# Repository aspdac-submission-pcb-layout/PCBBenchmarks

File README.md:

# A note for ASP-DAC 2021 reviewers

This repository was prepared from the original. The authors of contributed to many of these design. Therefore, some, but not all, license and author information was removed for review blinding. Some example license and author information that was not removed is located in the individual directories for each design (for example [bm1/bm1.license.txt](bm1/bm1.license.txt))

The unblinded repository contains full license and author citations for all designs.

# PCBBenchmarks

KiCad PCB benchmarks for automated layout.

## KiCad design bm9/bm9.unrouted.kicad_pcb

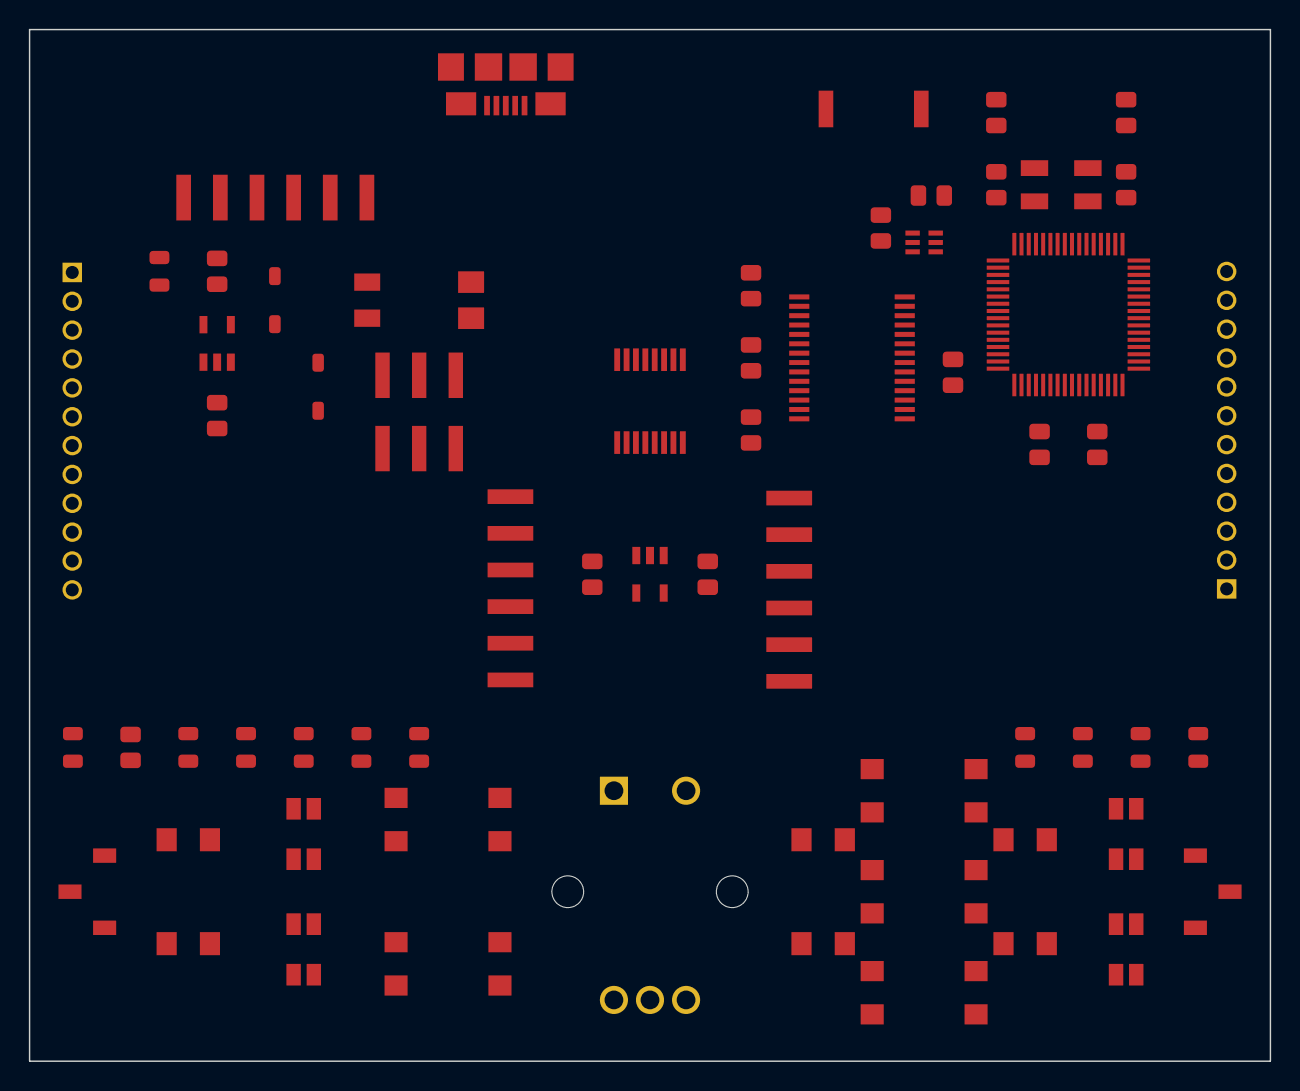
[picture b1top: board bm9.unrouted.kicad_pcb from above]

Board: 4 copper layers, 86.0 x 71.5 mm, 61 parts (0 on the bottom side), 63 nets, no tracks yet.

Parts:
A1: ANTENNA-CHIP; ANT-2.4GHZ-6.5X2.2MM
B1, B4, B5, B6, B7, B8, B9, B10: PUSHBUTTON_-4.5X4.5; 4.5MM_TACTILE_SWITCH_TL3305AF160QG
B2: BALUN0805; BALUN
B3: BATTERY-SPRING-SMD; WIRE-TERMINAL-1X2-2.5MM-SMD-AVX-009276002021106
C1, C8, C9: 0.1uF; CAPC2012X140_HS
C2: 0.75pF; CAPC2012X140_HS
C3: 22pF; CAPC2012X140_HS
C4, C10, C11, C12, C13, C16, C17: 1uF; CAPC2012X140_HS
C5, C6, C7: 10uF; CAPC2012X140_HS
C14, C15: 12pF; CAPC2012X140_HS
D1, D4, D5, D6: LED-2X-GREEN_RED; LED-2X-LTST-C155
D2, D3: 360mV; SOD3716X135_HS
E1: ROTARY-ENCODER-W_BUTTON-BOURNS-PEC12R-4217F; BOURNS-PEC12R
J1: USB-MICROA-AMPHENOL-10118192-0001LF; USB-MICROA-10118192-0001LF
J2, J3: 2.4K; JST-13-PTH
J4: AVR_SPI_PRG_6-SMD; 2X3-SMD
J7, J8: FRSKY-GIMBAL-2X-SERVO-SMD; 2X-SERVO-SMD
JP1: FTDI_BASIC-SMD; FTDI-BASIC-SMD
R1, R3, R13, R14, R15, R16, R17, R18: 510; RESC2012X60_HS
R2: 10K; RESC2012X60_HS
R7: 2.2K; RESC2012X60_HS
R8: 1.2K; RESC2012X60_HS
S1, S2: POWER-SWITCH-MFS201N-9-Z-SMD-VERTICAL; JS102011JCQN
U1: 3.3V; SOT23-DBV
U2: MCP73831T-2ACI/OT; SOT23-5
U3: FT232RLSSOP; SSOP28DB
U4: ATMEGA128RFA1; QFN-64
U5: DPDT-X2; SOP65P640X110-16
Y1: CRYSTAL5X3; CRYSTAL-SMD-5X3

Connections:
3V3: C12.1, C16.1, C17.1, D4.A2, J4.2, JP1.VCC, R2.2, R8.2, R13.2, R14.2, S2.1, U1.5, U4.23, U4.34, U4.44, U4.54, U4.59, U5.16
/BTN1/SCL: B4.3, B4.4, U4.25
/BTN2/SDA: B5.3, B5.4, U4.26
/BTN_CENTER: B9.1, B9.2, U4.53
/BTN_DOWN: B10.1, B10.2, U4.28
/BTN_LEFT: B7.1, B7.2, U4.51
/BTN_RIGHT: B8.1, B8.2, U4.52
/BTN_UP: B6.1, B6.2, U4.50
/CTS: U3.11, U5.2
/CTS-1: JP1.CTS, U5.1
/DTR: U3.2, U5.14
/DTR-0: C1.2, U5.15
/DTR-1: JP1.DTR, U5.13
/E1-A: E1.A, U4.40
/E1-B: E1.B, U4.41
/E1-BUT: E1.BUTA, U4.27
/FTDI_OUT: C4.2, C9.1, U3.4, U3.17
/GREF: J2.1, J2.4, J3.1, J3.4, J7.1, J7.4, J8.1, J8.4, R8.1
/MISO: J4.1, U4.39
/MOSI: J4.4, U4.38
/PITCH: J3.V, J8.V, U4.2
/RESET: B1.1, B1.2, C1.1, J4.5, R2.1, U4.12
/RF: D4.A1, U4.16
/ROLL: J3.H, J8.H, U4.1
/RXI: U3.5, U5.10
/RXI-0: U4.47, U5.11
/RXI-1: JP1.RXI, U5.9
/RXLED: D5.C2, U3.22
/SCK: J4.3, U4.37
/THROTTLE: J2.V, J7.V, U4.64
/TXLED: D5.C1, U3.23
/TXO: U3.1, U5.6
/TXO-0: U4.46, U5.7
/TXO-1: JP1.TXO, U5.5
/USB_D_N: J1.2, U3.16
/USB_D_P: J1.3, U3.15
/VBUS: C5.1, D1.A2, D2.A, J1.1, U2.4
/VREG_IN: C7.1, C8.1, C10.1, S1.1, U1.1, U1.3, U3.20
/YAW: J2.H, J7.H, U4.63
GND: B1.3, B1.4, B2.5, B3.2A, B3.2B, B4.1, B4.2, B5.1, B5.2, B6.3, B6.4, B7.3, B7.4, B8.3, B8.4, B9.3, B9.4, B10.3, B10.4, C2.2, C3.1, C4.1, C5.2, C6.2, C7.2, C8.2, C9.2, C10.2, C11.2, C12.2, C13.2, C14.2, C15.2, C16.2, C17.2, D1.C1, E1.BUTB, E1.C, J1.5, J1.6, J1.7, J1.8, J1.9, J1.10, J1.11, J2.3, J2.6, J3.3, J3.6, J4.6, J7.3, J7.6, J8.3, J8.6, JP1.GND, R7.2, R15.1, R16.1, R17.1, R18.1, S2.3, U1.2, U2.2, U3.7, U3.18, U3.21, U3.25, U3.26, U4.7, U4.10, U4.11, U4.20, U4.24, U4.33, U4.35, U4.45, U4.55, U4.58, U4.61, U5.8
unnamed: A1.FEED, B2.1, C2.1
unnamed: B2.2, C3.2
unnamed: B2.3, U4.9
unnamed: B2.4, U4.8
unnamed: B3.1A, B3.1B, C6.1, D3.A, U2.3
unnamed: C11.1, U4.21, U4.22
unnamed: C13.1, U4.60
unnamed: C14.1, U4.57, Y1.3
unnamed: C15.1, U4.56, Y1.1
unnamed: D1.A1, R3.1
unnamed: D1.C2, R1.1
unnamed: D4.C1, R15.2
unnamed: D4.C2, R16.2
unnamed: D5.A1, R14.1
unnamed: D5.A2, R13.1
unnamed: D6.A1, U4.15
unnamed: D6.A2, U4.14
unnamed: D6.C1, R18.2
unnamed: D6.C2, R17.2
unnamed: R1.2, R3.2, U2.1
unnamed: R7.1, U2.5
unnamed: S2.2, U5.4, U5.12
VBAT: D2.C, D3.C, S1.2

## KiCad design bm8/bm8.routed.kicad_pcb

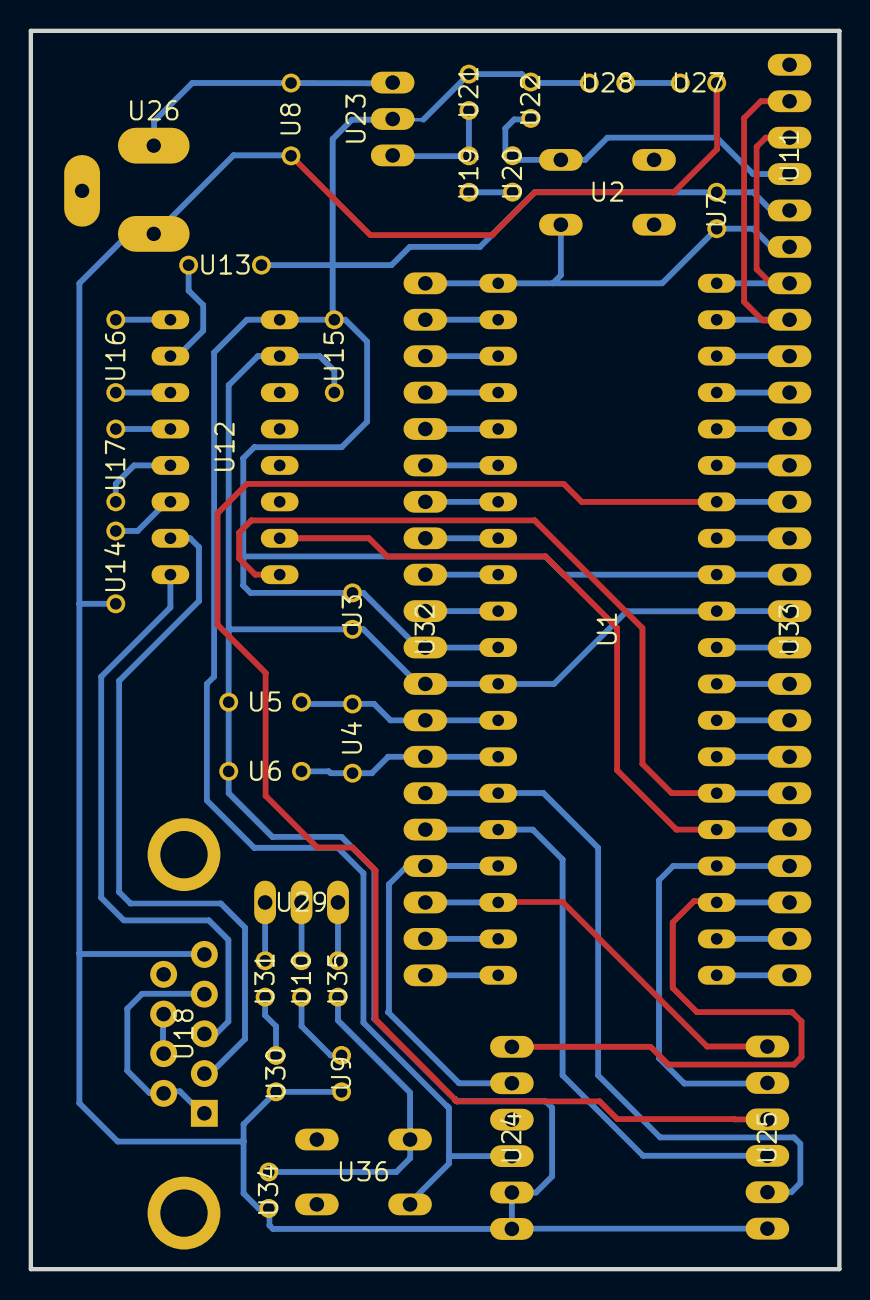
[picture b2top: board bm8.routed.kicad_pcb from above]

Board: 2 copper layers, 56.4 x 86.4 mm, 36 parts (0 on the bottom side), 58 nets.

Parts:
U1: DIL40
U2, U36: B3F-10XX
U3, U22: C025-024X044
U4: HC49_S
U5, U6, U13, U14, U15, U16, U17: C050-024X044
U7, U10, U19, U20, U21, U28, U31, U34, U35: V526-0
U8: C050-025X075
U9, U27, U30: LED3MM
U11, U24, U25: 1X06
U12: DIL16
U18: DB9
U23: 317TS
U26: 733980-62
U29: MA03-1
U32, U33: MA20-1

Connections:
/3.3V_SRC: U1.11, U1.32, U3.1, U7.1, U11.2, U12.16, U13.2, U15.1, U21.2, U22.1, U23.2, U24.3, U28.1, U32.10, U33.9, U36.1
/MRF_CS: U1.17, U24.5, U32.4
/MRF_INT: U1.34, U25.3, U33.7
/MRF_RESET: U1.15, U25.5, U32.6
/MRF_SCK: U1.18, U25.1, U32.3
/MRF_SDI: U1.23, U24.6, U33.18
/MRF_SDO: U1.24, U25.2, U33.17
/MRF_WAKE: U1.16, U25.4, U32.5
/N$17: U1.26, U12.9, U33.15
/N$21: U1.25, U12.10, U33.16
/OS1: U1.13, U4.1, U5.1, U32.8
/OSC2: U1.14, U4.2, U6.1, U32.7
GND: U1.12, U1.31, U2.1, U3.2, U5.2, U6.2, U8.2, U9.K, U11.3, U12.15, U14.1, U15.2, U18.5, U20.1, U22.2, U24.1, U24.2, U25.6, U26.1, U27.K, U30.K, U32.9, U33.10, U34.2
unnamed: U12.2, U13.1
unnamed: U12.6, U14.2
unnamed: U12.1, U16.1
unnamed: U12.3, U16.2
unnamed: U12.4, U17.1
unnamed: U12.5, U17.2
unnamed: U8.1, U23.3, U26.2
unnamed: U12.7, U18.2
unnamed: U12.8, U18.3
unnamed: U1.1, U2.3, U7.2, U11.1, U32.20
unnamed: U1.2, U32.19
unnamed: U1.3, U32.18
unnamed: U1.4, U32.17
unnamed: U1.5, U32.16
unnamed: U1.6, U32.15
unnamed: U1.7, U32.14
unnamed: U1.8, U32.13
unnamed: U1.9, U32.12
unnamed: U1.10, U32.11
unnamed: U1.19, U32.2
unnamed: U1.20, U32.1
unnamed: U1.21, U33.20
unnamed: U1.22, U33.19
unnamed: U1.27, U33.14
unnamed: U1.28, U33.13
unnamed: U1.29, U33.12
unnamed: U1.30, U33.11
unnamed: U1.33, U33.8
unnamed: U1.35, U33.6
unnamed: U1.36, U33.5
unnamed: U1.37, U33.4
unnamed: U1.38, U33.3
unnamed: U1.39, U11.5, U33.2
unnamed: U1.40, U11.4, U33.1
unnamed: U19.2, U21.1, U23.1
unnamed: U27.A, U28.2
unnamed: U30.A, U31.2
unnamed: U9.A, U10.2
unnamed: U34.1, U35.2, U36.3
unnamed: U29.3, U35.1
unnamed: U10.1, U29.2
unnamed: U29.1, U31.1
unnamed: U19.1, U20.2
unnamed: U18.1, U18.4, U18.6
unnamed: U18.7, U18.8

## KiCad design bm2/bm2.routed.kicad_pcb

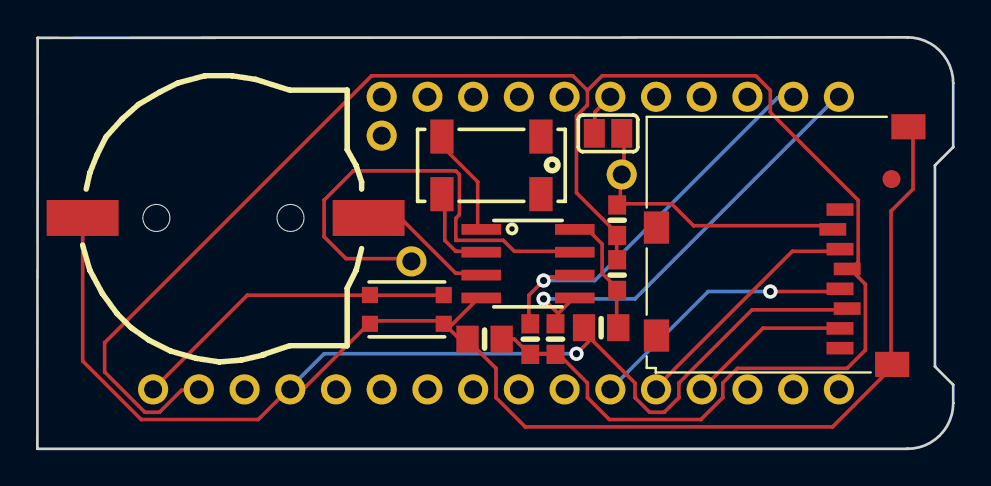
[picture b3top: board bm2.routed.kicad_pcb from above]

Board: 2 copper layers, 50.9 x 22.9 mm, 18 parts (0 on the bottom side), 15 nets.

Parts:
B1: cr1220; CR1220-2
C1, C2: 10uF; 0805-NO
FID1: FIDUCIAL_1MM
IC1: PCF8523T; SOIC8_150MIL
INT1: 1X01_ROUND
JP1: 1X11_ROUND
JP2: 1X16_ROUND
JP3: 1X01_ROUND
R1, R2: 10K; 0603-NO
R3: 100K; 0603-NO
R4: 1K; 0603-NO
SDCS: 1X01_ROUND
SJ1: SOLDERJUMPER_CLOSEDWIRE
SW1: KMR2; BTN_KMR2_4.6X2.8
X4: microsd; MICROSD
Y1: 32khz; CRYSTAL_8X3.8

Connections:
+3V3: C2.1, JP2.15, R1.2, R2.2, R3.2, R4.1, X4.4
CR1220: B1.+, IC1.3
CS: JP1.6, SJ1.1
GND: B1.-, C1.2, C2.2, IC1.4, JP2.13, SW1.A, SW1.A', X4.6, X4.MT1, X4.MT2
INT1: IC1.7, INT1.1
MISO: JP2.4, X4.7
MOSI: JP2.5, X4.3
unnamed: C1.1, IC1.8, R4.2
unnamed: IC1.1, Y1.P$4
unnamed: IC1.2, Y1.P$1
RESET: JP2.16, SW1.B, SW1.B'
SCK: JP2.6, X4.5
SCL: IC1.6, JP1.10, R2.1
SDA: IC1.5, JP1.11, R1.1
SD_CS: R3.1, SDCS.1, SJ1.2, X4.2

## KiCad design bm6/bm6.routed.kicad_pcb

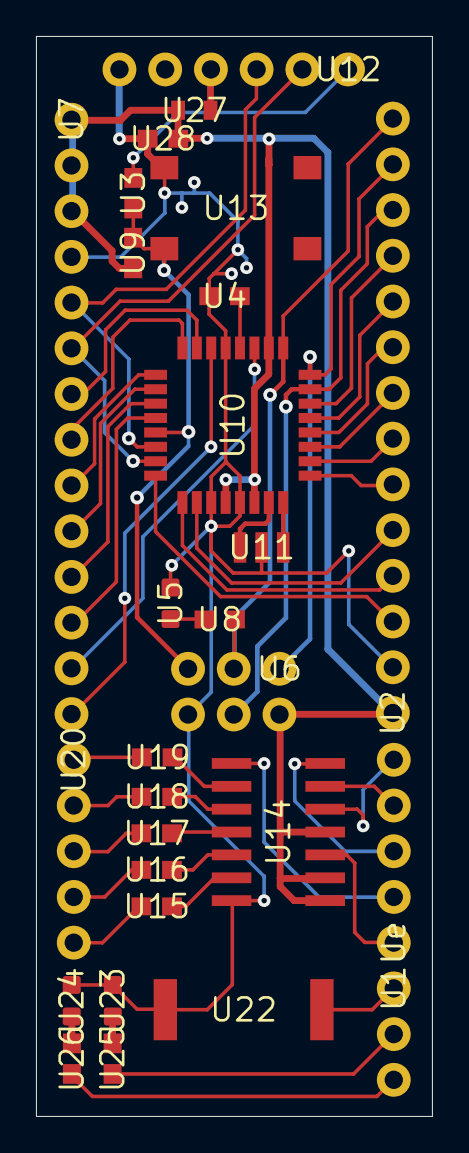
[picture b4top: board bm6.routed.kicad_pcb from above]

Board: 2 copper layers, 22.0 x 60.0 mm, 28 parts (0 on the bottom side), 51 nets.

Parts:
U1: 1X03
U2, U7: 1X14
U3, U4, U8, U9, U15, U16, U17, U18, U19, U25, U26, U28: 0603
U5, U23, U24: LED-0603
U6: 2X3
U10: TQFP32-08
U11: RESONATOR-SMD
U12: FTDI_BASIC
U13: TACTILE_SWITCH_SMD_6.2MM_TALL
U14: SO14
U20: 1X05
U22: PKMCS
U27: FUSC1608X100N
Ue: 1X05

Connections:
/A0: U7.7, U10.23
/A1: U7.8, U10.24
/A2: U7.9, U10.25
/A3: U7.10, U10.26
/A4: U7.11, U10.27
/A5: U7.12, U10.28
/A6: U7.13, U10.19
/A7: U7.14, U10.22
/D2: U2.3, U10.32
/D3: U2.4, U10.1
/D4: U2.5, U10.2
/D5: U2.6, U10.9
/D6: U2.7, U10.10
/D7: U2.8, U10.11
/D8: U2.9, U10.12
/D9: U2.10, U10.13
/D10: U2.11, U10.14
/DTR: U3.1, U12.DTR
/GO: U14.3, Ue.1
/MISO: U2.13, U6.1, U10.16
/MOSI: U2.12, U6.4, U10.15
/OUT1: U14.8, Ue.2
/OUT2: U14.7, Ue.3
/OUT3: U14.6, Ue.4
/OUT4: U14.5, Ue.5
/RST: U3.2, U6.5, U9.1, U10.29, U13.B2
/RXI: U7.5, U10.30, U12.TXO
/SCK: U2.14, U6.3, U8.1, U10.17
/TXO: U7.6, U10.31, U12.RXI
GND: U2.2, U4.2, U5.C, U6.6, U7.4, U10.3, U10.5, U10.21, U11.2, U12.GND, U13.A2, U14.14, U22.1, U23.C, U24.C, U28.2
unnamed: U4.1, U10.20
unnamed: U5.A, U8.2
unnamed: U23.A, U25.1
unnamed: U24.A, U26.1
unnamed: U12.VCC, U27.1
unnamed: U14.9, U19.2
unnamed: U14.10, U18.2
unnamed: U14.11, U17.2
unnamed: U14.12, U16.2
unnamed: U14.13, U15.2
unnamed: U19.1, U20.1
unnamed: U18.1, U20.2
unnamed: U17.1, U20.3
unnamed: U16.1, U20.4
unnamed: U15.1, U20.5
unnamed: U1.1, U22.2
unnamed: U1.2, U25.2
unnamed: U1.3, U26.2
unnamed: U10.7, U11.3
unnamed: U10.8, U11.1
VCC: U2.1, U6.2, U7.1, U7.2, U7.3, U9.2, U10.4, U10.6, U10.18, U14.1, U14.2, U14.4, U27.2, U28.1

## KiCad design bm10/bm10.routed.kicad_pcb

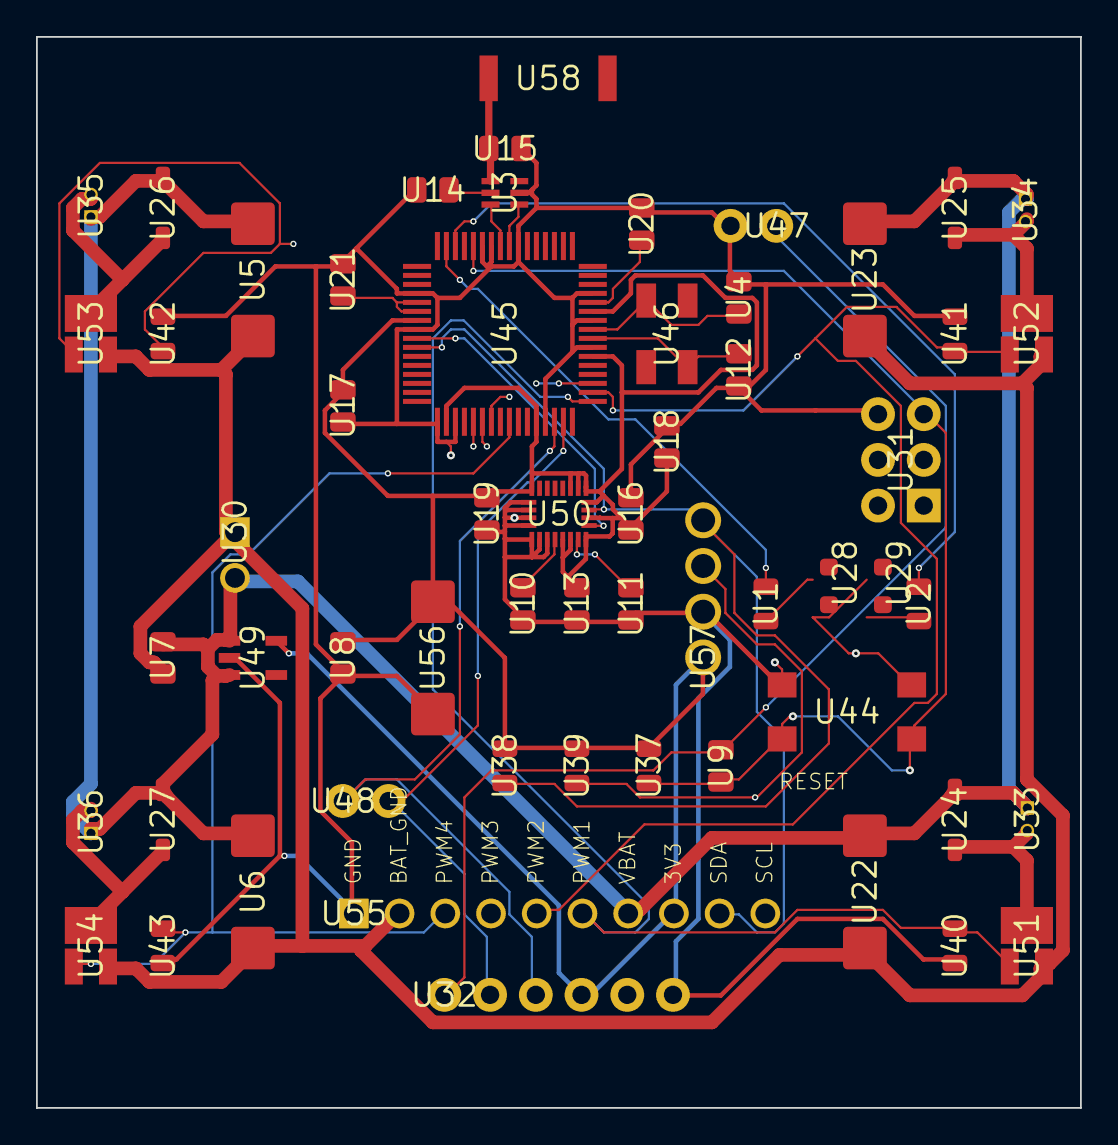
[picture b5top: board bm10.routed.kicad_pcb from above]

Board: 4 copper layers, 58.0 x 59.5 mm, 58 parts (0 on the bottom side), 35 nets.

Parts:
U1, U2, U37, U38, U39, U40, U41, U42, U43: RESC2012X60_HS
U3: BALUN
U4, U7, U8, U9, U10, U11, U12, U13, U14, U15, U16, U17, U18, U19, U20, U21: CAPC2012X140_HS
U5, U6, U22, U23, U56: CAPMP7343X310_HS
U24, U25, U26, U27: SOD3716X135_HS
U28, U29: LEDSC125X200X120-2_HS
U30: MALE_HEADER_2X1_0.1IN
U31: 2X3-NS
U32: FTDI_BASIC
U33, U34, U35, U36: MOLEX-0530470210
U44: 4.5MM_TACTILE_SWITCH_TL3305AF160QG
U45: QFN-64
U46: CRYSTAL-SMD-5X3
U47: FTDI_BASIC_2PIN_2
U48: FTDI_BASIC_2PIN_1
U49: SOT23-DBV
U50: NEW_IMU_MEDIUM
U51, U52, U53, U54: N_FET_SI2302CDS-T1-E3CT-ND
U55: HDRV10W63P254_10X1_2540X254H838_HS
U57: HDRVR4W80P254_1X4_1066X254X850B
U58: ANT-2.4GHZ-6.5X2.2MM

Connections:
3V3: U8.1, U13.1, U16.1, U17.1, U18.1, U19.1, U32.VCC, U37.2, U38.2, U39.2, U45.23, U45.34, U45.44, U45.54, U45.59, U49.5, U50.CS_A/G, U50.CS_M, U50.DEN_A/G, U50.SDO_A/G, U50.SDO_M, U50.VDD1, U50.VDD2, U50.VDDIO, U50.VDDIO2, U55.8, U56.1, U57.1
/DTR: U9.1, U32.DTR, U47.DTR
/LED1: U2.2, U45.14
/LED2: U1.2, U45.15
/MISO: U31.1, U45.39
/MOSI: U31.4, U45.38
/PWM1: U40.1, U45.49, U51.G, U55.6
/PWM2: U41.1, U45.50, U52.G, U55.5
/PWM3: U42.1, U45.51, U53.G, U55.4
/PWM4: U43.1, U45.41, U54.G, U55.3
/RESET: U9.2, U31.5, U37.1, U44.3, U44.4, U45.12
/RX0: U32.TXO, U45.46, U48.TXO
/SCK: U31.3, U45.37
/SCL: U39.1, U45.25, U50.SCL/SPC, U55.10, U57.3
/SDA: U38.1, U45.26, U50.SDA/SDI/SDO, U55.9, U57.4
/TX0: U32.RXI, U45.47, U48.RXI
BAT_GND: U5.2, U6.2, U7.2, U22.2, U23.2, U30.1, U51.S, U52.S, U53.S, U54.S, U55.2
GND: U3.5, U4.2, U8.2, U10.2, U11.2, U12.2, U13.2, U14.2, U15.2, U16.2, U17.2, U18.2, U19.2, U20.2, U21.2, U28.2, U29.1, U31.6, U32.GND, U40.2, U41.2, U42.2, U43.2, U44.1, U44.2, U45.7, U45.10, U45.11, U45.20, U45.24, U45.33, U45.35, U45.45, U45.55, U45.58, U45.61, U47.CTS, U49.2, U50.GND1, U50.GND2, U50.RES1, U50.RES2, U50.RES3, U50.RES4, U50.RES5, U55.1, U56.2, U57.2
unnamed: U3.1, U15.1, U58.FEED
unnamed: U3.2, U14.1
unnamed: U3.3, U45.9
unnamed: U3.4, U45.8
unnamed: U4.1, U45.57, U46.1
unnamed: U12.1, U45.56, U46.3
unnamed: U20.1, U45.60
unnamed: U21.1, U45.21, U45.22
unnamed: U10.1, U50.CAP
unnamed: U11.1, U50.C1
unnamed: U24.A, U33.2, U51.D
unnamed: U25.A, U34.2, U52.D
unnamed: U26.A, U35.2, U53.D
unnamed: U27.A, U36.2, U54.D
unnamed: U1.1, U28.1
unnamed: U2.1, U29.2
VBAT: U5.1, U6.1, U7.1, U22.1, U23.1, U24.C, U25.C, U26.C, U27.C, U30.2, U33.1, U34.1, U35.1, U36.1, U49.1, U49.3, U55.7

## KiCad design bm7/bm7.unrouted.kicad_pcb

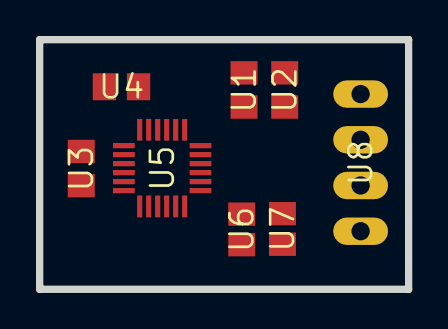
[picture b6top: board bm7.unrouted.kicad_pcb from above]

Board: 2 copper layers, 20.5 x 13.9 mm, 8 parts (0 on the bottom side), 9 nets, no tracks yet.

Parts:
U1, U2, U3, U4: C0805
U5: LGA-24
U6, U7: R0805
U8: MA04-1

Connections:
/SCL: U5.21, U8.2
/SDA: U5.24, U8.3
GND: U1.2, U2.2, U4.1, U5.2, U5.3, U5.4, U5.5, U5.6, U5.22, U5.23, U8.4
unnamed: U3.1, U5.9
unnamed: U3.2, U5.8
unnamed: U4.2, U5.7
unnamed: U5.19, U6.1
unnamed: U5.20, U7.1
VDD: U1.1, U2.1, U5.15, U5.16, U5.17, U5.18, U6.2, U7.2, U8.1

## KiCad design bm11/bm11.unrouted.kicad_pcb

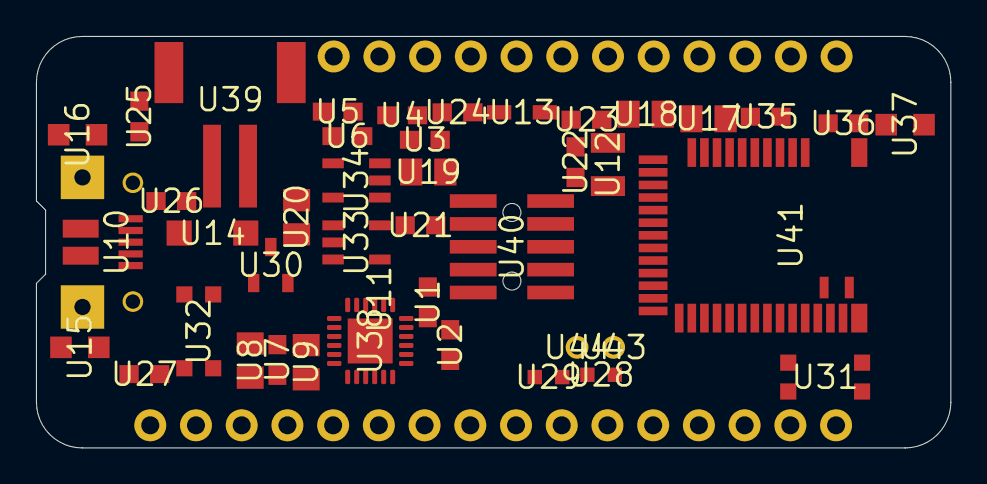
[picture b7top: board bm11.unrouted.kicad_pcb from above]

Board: 2 copper layers, 50.8 x 22.9 mm, 46 parts (0 on the bottom side), 51 nets, no tracks yet.

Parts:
MS1: MS1
MS2: MS2
TP2: FRST; PAD-1.5X2.0
U1, U2, U3, U4, U5, U6, U7, U21, U22, U23, U24, U25, U26, U27, U35, U36: 0603-NO
U8, U9, U17, U18, U19, U20: 0805-NO
U10: 4UCONN_20329_V2
U11: SOLDERJUMPER_CLOSEDWIRE
U12: XTAL3215
U13: SOD-323
U14: SOD-123
U15, U16, U37: CHIPLED_0805_NOOUTLINE
U28, U29: _0603MP
U30: SOT23-R
U31, U32: BTN_KMR2_4.6X2.8
U33, U34: SOT23-5
U38: QFN24_4MM_SMSC
U39: JSTPH2
U40: 2X05_1.27MM_BOX_POSTS
U41: BLE_MODULE_RAYTAC_MDBT42
U43, U44: 1X01_2MM

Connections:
3.3V: MS1.2, MS1.3, U7.1, U8.1, U13.C, U18.1, U24.2, U34.5, U38.5, U38.6, U38.7, U40.1, U41.11
/A0/0.02: MS1.5, U41.15
/A1/0.03: MS1.6, U41.16
/A2/0.04: MS1.7, U41.17
/A3/0.05: MS1.8, U41.18
/A4/0.28: MS1.9, U41.5
/A5/0.29: MS1.10, U41.6
/A6/P0.30: MS2.20, U41.7
/A7/P0.31: MS2.21, U4.1, U5.2, U6.1, U41.8
/DFU: MS1.16, U31.B, U31.B', U41.34
/DTR: U1.2, U38.23
/EN: MS2.27, U3.1, U34.3
/FRST: TP2.P$1, U41.38
/LED1: U25.2, U41.31
/LED2: U36.2, U41.33
/MISO: MS1.13, U41.28
/MOSI: MS1.12, U41.27
/P0.07: MS2.23, U41.20
/P0.09/NFC1: U29.1, U41.22, U44.1
/P0.10/NFC2: U28.1, U41.23, U43.1
/P0.11: MS2.22, U41.25
/P0.15: MS2.24, U41.29
/P0.16: MS2.25, U41.30
/P0.27: MS2.19, U41.4
/RESET: MS1.1, U11.1, U13.A, U24.1, U32.A, U32.A', U40.10, U41.35
/RXD: MS1.14, U2.2, U41.21
/SCK: MS1.11, U41.26
/SCL: MS2.18, U41.3
/SDA: MS2.17, U41.2
/SWCLK: U40.4, U41.36
/SWDIO: U40.2, U41.37
/SWO: U40.6, U41.32
/TXD: MS1.15, U38.20, U41.19
/USBD+: U10.D+, U38.3
/USBD-: U10.D-, U38.4
GND: MS1.4, U4.2, U6.2, U7.2, U8.2, U9.2, U10.BASE@1, U10.BASE@2, U10.GND, U10.SPRT@1, U10.SPRT@2, U16.C, U18.2, U19.2, U20.2, U21.2, U22.2, U23.2, U26.1, U28.2, U29.2, U31.A, U31.A', U32.B, U32.B', U33.2, U34.2, U35.2, U37.C, U38.2, U38.THERM, U39.1, U40.3, U40.5, U40.7, U40.9, U41.1, U41.12, U41.24, U41.39
unnamed: U12.P$1, U23.1, U41.13
unnamed: U12.P$2, U22.1, U41.14
unnamed: U17.1, U35.1, U41.9
unnamed: U3.2, U14.C, U19.1, U30.2, U34.1
unnamed: U9.1, U38.16
unnamed: U1.1, U11.2
unnamed: U15.C, U27.1
unnamed: U16.A, U25.1
unnamed: U36.1, U37.A
unnamed: U17.2, U41.10
unnamed: U27.2, U33.1
unnamed: U21.1, U33.5
unnamed: U2.1, U38.21
VBAT: MS2.28, U5.1, U20.1, U30.3, U33.3, U39.2
VBUS: MS2.26, U10.VBUS, U14.A, U15.A, U26.2, U30.1, U33.4, U38.8

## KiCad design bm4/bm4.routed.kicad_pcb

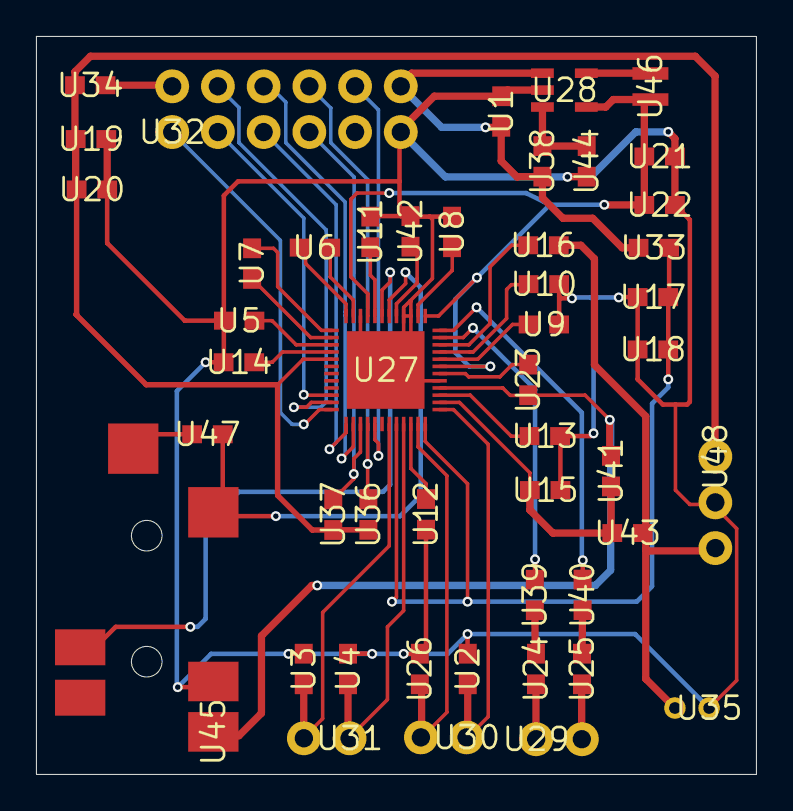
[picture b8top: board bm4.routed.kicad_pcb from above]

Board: 2 copper layers, 40.0 x 41.0 mm, 48 parts (0 on the bottom side), 47 nets.

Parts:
U1, U2, U3, U4, U5, U6, U7, U8, U9, U10, U11, U12, U13, U14, U15, U16, U17, U18, U19, U20, U21, U22, U23, U24, U25, U26, U33, U34, U36, U37, U38, U39, U40, U41, U42, U43, U44, U47: 0603
U27: QFN50P700X700X100-49N
U28: SOT95P284X122-5N
U29, U30, U31: 1X02
U32: 2X6
U35: CMC-2242PBL-A
U45: SJ-43514-SMT-TR
U46: NRH2412T2R2MNGH
U48: 1X03

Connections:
3.3V: U32.2, U34.2
5V: U1.2, U28.1, U32.12, U33.2, U38.1
/1.8VDD: U21.1, U22.1, U27.7, U27.13, U27.21, U28.4, U46.2
/3.3VDD: U19.1, U20.1, U27.29, U34.1, U36.1, U37.1, U48.1
/CPVREF: U27.17, U42.1
/HPOL: U27.18, U45.2, U47.1
/HPOR: U27.19, U45.3
/IN1P: U23.1, U27.4, U41.2, U45.1
/IN2P: U16.1, U35.2, U43.2, U48.3
/LOUTL: U27.11, U39.1
/LOUTR: U27.12, U40.1
/MICBIAS1: U15.2, U27.2, U41.1, U43.1
/SPKVDD: U17.1, U18.1, U27.44, U27.48, U33.1
/SPOLN: U26.1, U27.47, U30.2
/SPOLP: U2.1, U27.1, U30.1
/SPORN: U3.1, U27.43, U31.2
/SPORP: U4.1, U27.45, U31.1
/XADUIO_I2S0_BCLK: U27.37, U32.5
/XADUIO_I2S0_LRCKL: U27.36, U32.1
/XADUIO_SCL: U27.39, U32.7, U37.2
/XAUDIO_I2S0_DIN: U27.35, U32.4
/XAUDIO_I2S0_DOUT: U27.34, U32.3
/XAUDIO_I2S0_MCLK: U27.38, U32.6
/XAUDIO_IRQ: U27.41, U32.10
/XAUDIO_SDA: U27.40, U32.8, U36.2
GND: U1.1, U2.2, U3.2, U4.2, U5.2, U8.1, U9.1, U10.1, U11.2, U12.1, U13.1, U14.1, U15.1, U17.2, U18.2, U19.2, U20.2, U21.2, U22.2, U26.2, U27.5, U27.15, U27.16, U27.22, U27.49, U28.2, U32.11, U35.1, U42.2, U44.1, U45.4, U48.2
unnamed: U11.1, U27.20
unnamed: U23.2, U27.6
unnamed: U24.1, U39.2
unnamed: U24.2, U29.1
unnamed: U25.1, U40.2
unnamed: U25.2, U29.2
unnamed: U5.1, U27.27
unnamed: U6.1, U27.24
unnamed: U6.2, U27.23
unnamed: U7.1, U27.25
unnamed: U7.2, U27.26
unnamed: U8.2, U27.14
unnamed: U9.2, U27.8
unnamed: U10.2, U27.9
unnamed: U12.2, U27.46
unnamed: U13.2, U27.3
unnamed: U14.2, U27.28
unnamed: U16.2, U27.10
unnamed: U28.3, U38.2, U44.2
unnamed: U28.5, U46.1
unnamed: U45.5, U47.2

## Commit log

2020-08-11 Initial
    Initial commit
